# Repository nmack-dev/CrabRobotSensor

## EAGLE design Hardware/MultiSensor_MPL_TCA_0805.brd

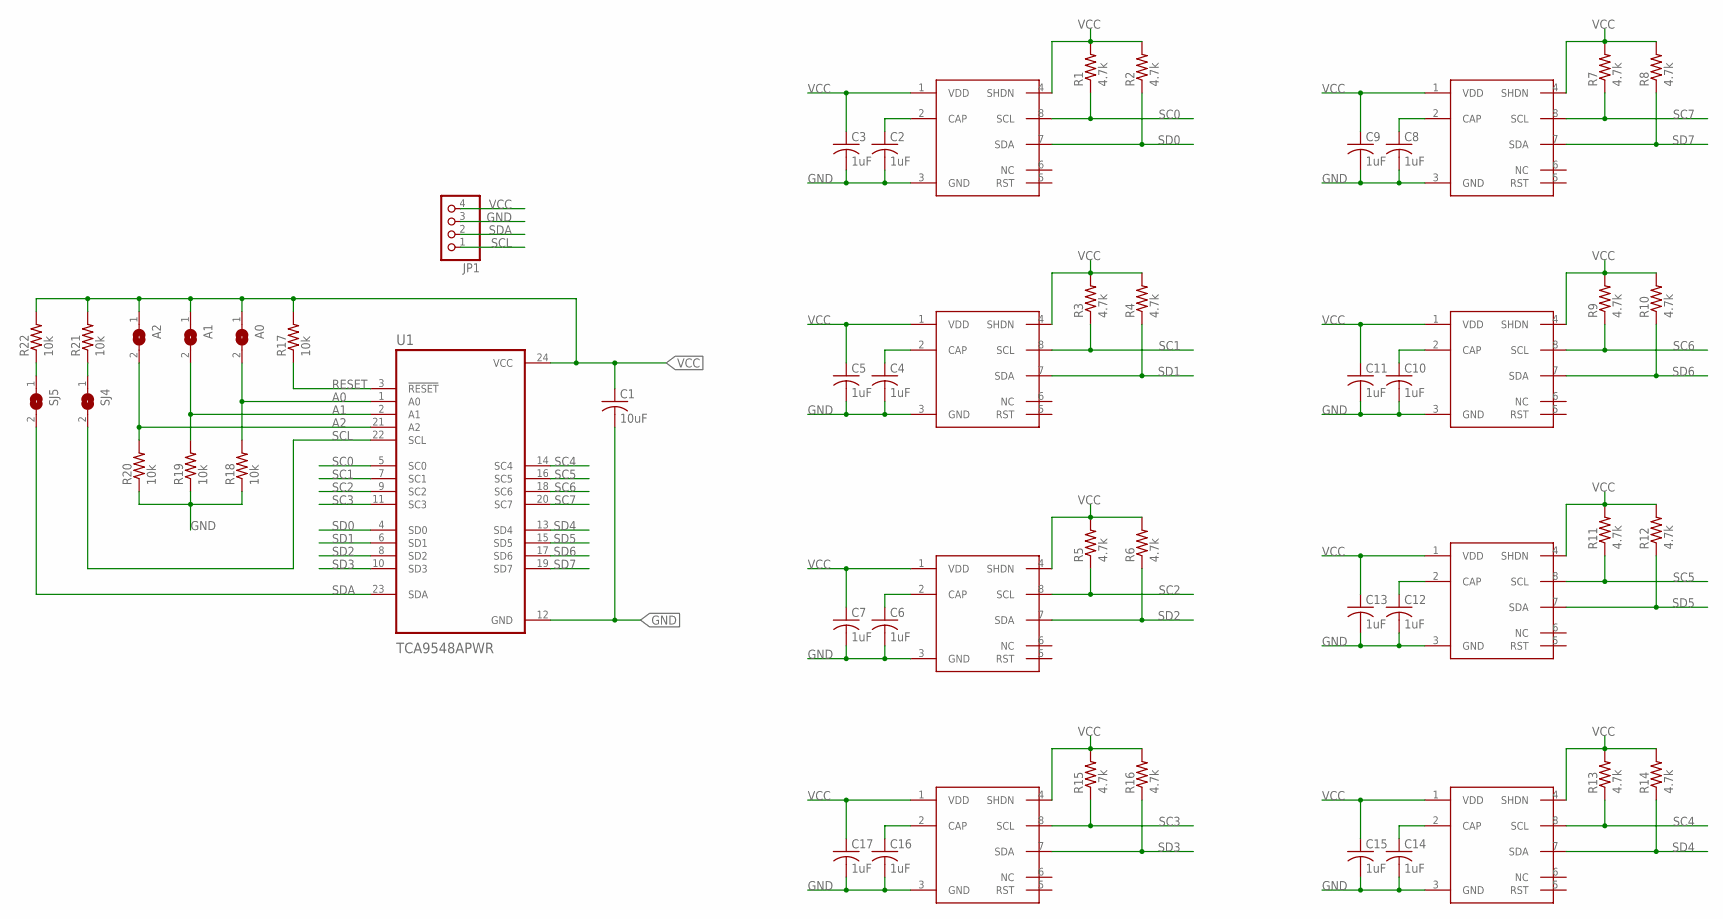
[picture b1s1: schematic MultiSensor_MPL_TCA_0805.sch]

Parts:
A0, A1, A2: SJ
B1, B2, B3, B4, B5, B6, B7, B8: MPL115A2T1
C1: 10uF; C1206
C2, C3, C4, C5, C6, C7, C8, C9, C10, C11, C12, C13, C14, C15, C16, C17: 1uF; C0805
JP1: PINHD-1X4; 1X04
R1, R2, R3, R4, R5, R6, R7, R8, R9, R10, R11, R12, R13, R14, R15, R16: 4.7k; R0805
R17, R18, R19, R20, R21, R22: 10k; R0805
SJ4, SJ5: SJ
U1: TCA9548APWR; SOP65P640X120-24N

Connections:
A0: A0.2, R18.2, U1.1 (A0)
A1: A1.2, R19.2, U1.2 (A1)
A2: A2.2, R20.2, U1.21 (A2)
CAP1: B1.2 (CAP), C2.1
CAP2: B2.2 (CAP), C4.1
CAP3: B3.2 (CAP), C6.1
CAP4: B8.2 (CAP), C16.1
CAP5: B7.2 (CAP), C14.1
CAP6: B6.2 (CAP), C12.1
CAP7: B5.2 (CAP), C10.1
CAP8: B4.2 (CAP), C8.1
GND: B1.3 (GND), B2.3 (GND), B3.3 (GND), B4.3 (GND), B5.3 (GND), B6.3 (GND), B7.3 (GND), B8.3 (GND), C1.2, C2.2, C3.2, C4.2, C5.2, C6.2, C7.2, C8.2, C9.2, C10.2, C11.2, C12.2, C13.2, C14.2, C15.2, C16.2, C17.2, JP1.3, R18.1, R19.1, R20.1, U1.12 (GND)
unnamed: R22.1, SJ5.1
unnamed: R21.1, SJ4.1
RESET: R17.1, U1.3 (!RESET)
SC0: B1.8 (SCL), R1.1, U1.5 (SC0)
SC1: B2.8 (SCL), R3.1, U1.7 (SC1)
SC2: B3.8 (SCL), R5.1, U1.9 (SC2)
SC3: B8.8 (SCL), R15.1, U1.11 (SC3)
SC4: B7.8 (SCL), R13.1, U1.14 (SC4)
SC5: B6.8 (SCL), R11.1, U1.16 (SC5)
SC6: B5.8 (SCL), R9.1, U1.18 (SC6)
SC7: B4.8 (SCL), R7.1, U1.20 (SC7)
SCL: JP1.1, SJ4.2, U1.22 (SCL)
SD0: B1.7 (SDA), R2.1, U1.4 (SD0)
SD1: B2.7 (SDA), R4.1, U1.6 (SD1)
SD2: B3.7 (SDA), R6.1, U1.8 (SD2)
SD3: B8.7 (SDA), R16.1, U1.10 (SD3)
SD4: B7.7 (SDA), R14.1, U1.13 (SD4)
SD5: B6.7 (SDA), R12.1, U1.15 (SD5)
SD6: B5.7 (SDA), R10.1, U1.17 (SD6)
SD7: B4.7 (SDA), R8.1, U1.19 (SD7)
SDA: JP1.2, SJ5.2, U1.23 (SDA)
VCC: A0.1, A1.1, A2.1, B1.1 (VDD), B1.4 (SHDN), B2.1 (VDD), B2.4 (SHDN), B3.1 (VDD), B3.4 (SHDN), B4.1 (VDD), B4.4 (SHDN), B5.1 (VDD), B5.4 (SHDN), B6.1 (VDD), B6.4 (SHDN), B7.1 (VDD), B7.4 (SHDN), B8.1 (VDD), B8.4 (SHDN), C1.1, C3.1, C5.1, C7.1, C9.1, C11.1, C13.1, C15.1, C17.1, JP1.4, R1.2, R2.2, R3.2, R4.2, R5.2, R6.2, R7.2, R8.2, R9.2, R10.2, R11.2, R12.2, R13.2, R14.2, R15.2, R16.2, R17.2, R21.2, R22.2, U1.24 (VCC)

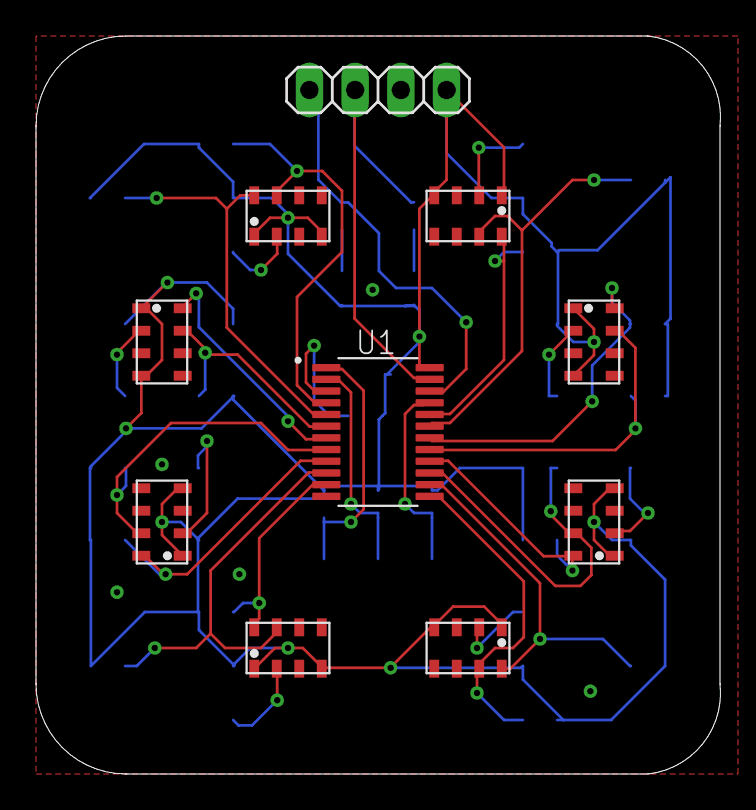
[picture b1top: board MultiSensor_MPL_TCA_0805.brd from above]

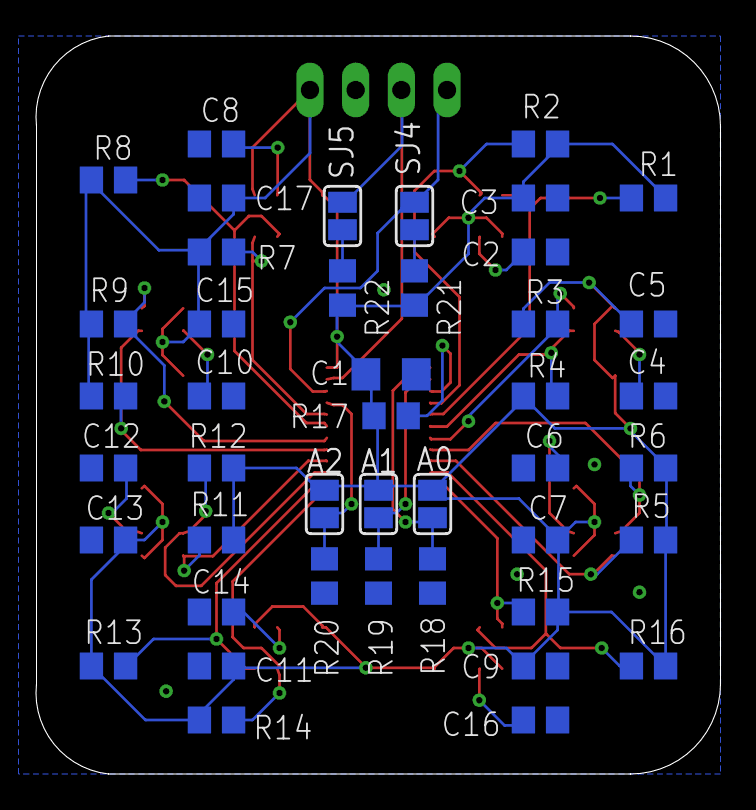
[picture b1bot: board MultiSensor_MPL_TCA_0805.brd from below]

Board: 2 copper layers, 38.0 x 41.0 mm, 54 parts (44 on the bottom side), 34 nets.

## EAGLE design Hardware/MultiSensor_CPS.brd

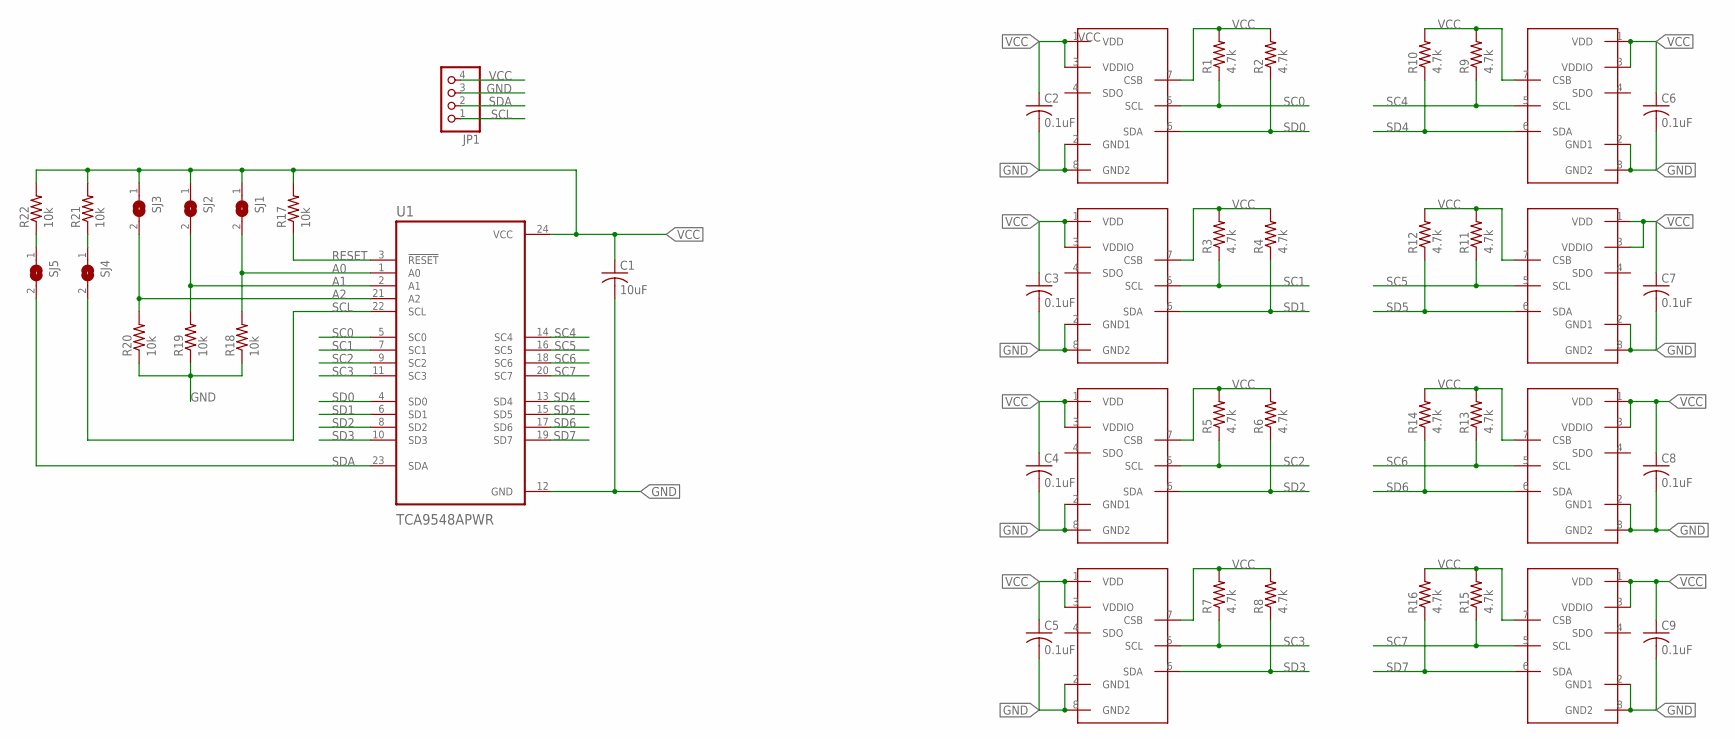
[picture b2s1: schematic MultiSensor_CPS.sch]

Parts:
B1, B2, B3, B4, B5, B6, B8, B9: CPS123
C1: 10uF; C0805
C2, C3, C4, C5, C6, C7, C8, C9: 0.1uF; C0805
JP1: PINHD-1X4; 1X04
R1, R2, R3, R4, R5, R6, R7, R8, R9, R10, R11, R12, R13, R14, R15, R16: 4.7k; R0805
R17, R18, R19, R20, R21, R22: 10k; R0805
SJ1, SJ2, SJ3, SJ4, SJ5: SJ
U1: TCA9548APWR; SOP65P640X120-24N

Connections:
A0: R18.2, SJ1.2, U1.1 (A0)
A1: R19.2, SJ2.2, U1.2 (A1)
A2: R20.2, SJ3.2, U1.21 (A2)
GND: B1.2 (GND1), B1.8 (GND2), B2.2 (GND1), B2.8 (GND2), B3.2 (GND1), B3.8 (GND2), B4.2 (GND1), B4.8 (GND2), B5.2 (GND1), B5.8 (GND2), B6.2 (GND1), B6.8 (GND2), B8.2 (GND1), B8.8 (GND2), B9.2 (GND1), B9.8 (GND2), C1.2, C2.2, C3.2, C4.2, C5.2, C6.2, C7.2, C8.2, C9.2, JP1.3, R18.1, R19.1, R20.1, U1.12 (GND)
unnamed: R22.1, SJ5.1
unnamed: R21.1, SJ4.1
RESET: R17.1, U1.3 (!RESET)
SC0: B5.5 (SCL), R1.1, U1.5 (SC0)
SC1: B1.5 (SCL), R3.1, U1.7 (SC1)
SC2: B2.5 (SCL), R5.1, U1.9 (SC2)
SC3: B9.5 (SCL), R7.1, U1.11 (SC3)
SC4: B6.5 (SCL), R9.1, U1.14 (SC4)
SC5: B4.5 (SCL), R11.1, U1.16 (SC5)
SC6: B3.5 (SCL), R13.1, U1.18 (SC6)
SC7: B8.5 (SCL), R15.1, U1.20 (SC7)
SCL: JP1.1, SJ4.2, U1.22 (SCL)
SD0: B5.6 (SDA), R2.1, U1.4 (SD0)
SD1: B1.6 (SDA), R4.1, U1.6 (SD1)
SD2: B2.6 (SDA), R6.1, U1.8 (SD2)
SD3: B9.6 (SDA), R8.1, U1.10 (SD3)
SD4: B6.6 (SDA), R10.1, U1.13 (SD4)
SD5: B4.6 (SDA), R12.1, U1.15 (SD5)
SD6: B3.6 (SDA), R14.1, U1.17 (SD6)
SD7: B8.6 (SDA), R16.1, U1.19 (SD7)
SDA: JP1.2, SJ5.2, U1.23 (SDA)
VCC: B1.1 (VDD), B1.3 (VDDIO), B1.7 (CSB), B2.1 (VDD), B2.3 (VDDIO), B2.7 (CSB), B3.1 (VDD), B3.3 (VDDIO), B3.7 (CSB), B4.1 (VDD), B4.3 (VDDIO), B4.7 (CSB), B5.1 (VDD), B5.3 (VDDIO), B5.7 (CSB), B6.1 (VDD), B6.3 (VDDIO), B6.7 (CSB), B8.1 (VDD), B8.3 (VDDIO), B8.7 (CSB), B9.1 (VDD), B9.3 (VDDIO), B9.7 (CSB), C1.1, C2.1, C3.1, C4.1, C5.1, C6.1, C7.1, C8.1, C9.1, JP1.4, R1.2, R2.2, R3.2, R4.2, R5.2, R6.2, R7.2, R8.2, R9.2, R10.2, R11.2, R12.2, R13.2, R14.2, R15.2, R16.2, R17.2, R21.2, R22.2, SJ1.1, SJ2.1, SJ3.1, U1.24 (VCC)

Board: 2 copper layers, 46 parts (36 on the bottom side), 26 nets, no tracks yet.

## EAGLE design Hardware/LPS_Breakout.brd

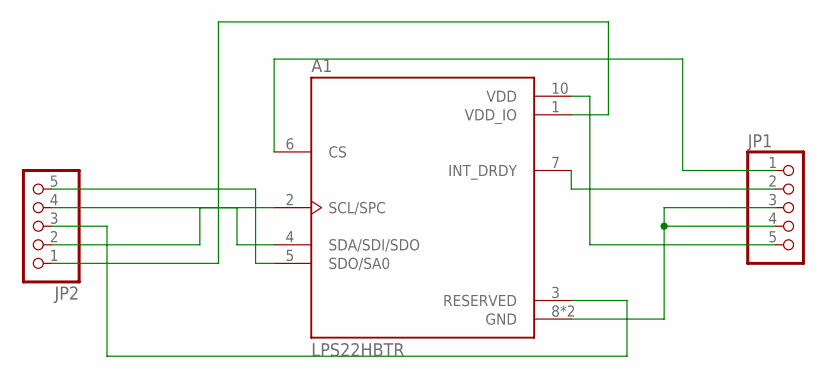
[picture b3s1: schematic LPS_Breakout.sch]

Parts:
A1: LPS22HBTR; PQFN50P200X200X80-10N
JP1, JP2: PINHD-1X5; 1X05

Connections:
unnamed: A1.1 (VDD_IO), JP2.1
unnamed: A1.2 (SCL/SPC), JP2.2
unnamed: A1.3 (RESERVED), JP2.3
unnamed: A1.4 (SDA/SDI/SDO), JP2.4
unnamed: A1.5 (SDO/SA0), JP2.5
unnamed: A1.6 (CS), JP1.1
unnamed: A1.7 (INT_DRDY), JP1.2
unnamed: A1.8 (GND), A1.9 (GND), JP1.3, JP1.4
unnamed: A1.10 (VDD), JP1.5

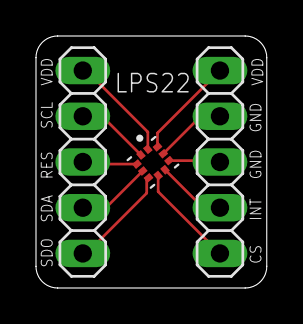
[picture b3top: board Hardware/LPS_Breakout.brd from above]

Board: 2 copper layers, 12.8 x 14.0 mm, 3 parts (0 on the bottom side), 9 nets.

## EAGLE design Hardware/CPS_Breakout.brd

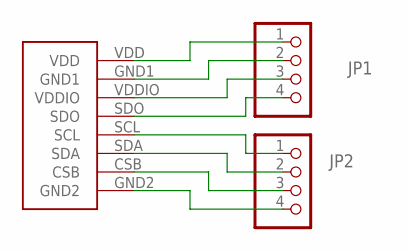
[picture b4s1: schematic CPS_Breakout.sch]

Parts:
B1: CPS123
JP1, JP2: PINHD-1X4; 1X04

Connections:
unnamed: B1.GND1, JP1.2
unnamed: B1.VDD, JP1.1
unnamed: B1.VDDIO, JP1.3
unnamed: B1.SDO, JP1.4
unnamed: B1.SCL, JP2.1
unnamed: B1.SDA, JP2.2
unnamed: B1.CSB, JP2.3
unnamed: B1.GND2, JP2.4

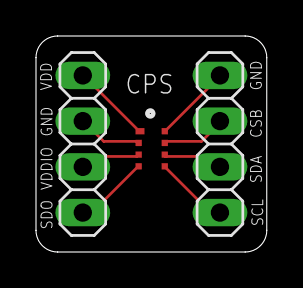
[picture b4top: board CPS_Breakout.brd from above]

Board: 2 copper layers, 12.8 x 12.0 mm, 3 parts (0 on the bottom side), 8 nets.

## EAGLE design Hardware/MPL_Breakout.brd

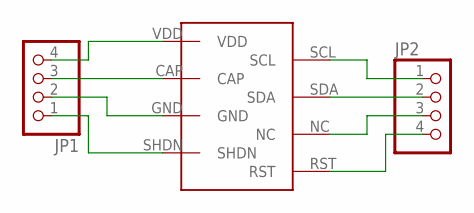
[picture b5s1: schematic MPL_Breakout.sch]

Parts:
B1: MPL115A2T1
JP1, JP2: PINHD-1X4; 1X04

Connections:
unnamed: B1.VDD, JP1.4
unnamed: B1.CAP, JP1.3
unnamed: B1.GND, JP1.2
unnamed: B1.SHDN, JP1.1
unnamed: B1.RST, JP2.4
unnamed: B1.NC, JP2.3
unnamed: B1.SDA, JP2.2
unnamed: B1.SCL, JP2.1

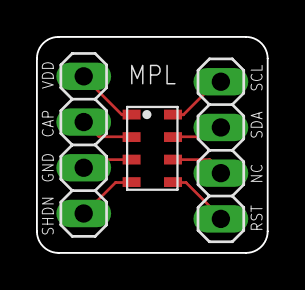
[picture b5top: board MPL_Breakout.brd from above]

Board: 2 copper layers, 12.8 x 12.0 mm, 3 parts (0 on the bottom side), 8 nets.

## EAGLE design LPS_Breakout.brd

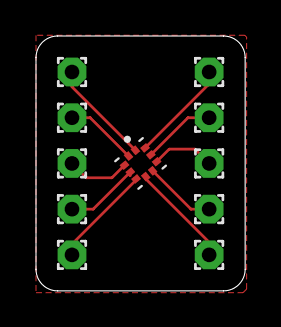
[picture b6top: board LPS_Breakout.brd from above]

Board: 2 copper layers, 11.6 x 14.2 mm, 11 parts (0 on the bottom side), 9 nets.

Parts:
A1: LPS22HBTR; PQFN50P200X200X80-10N
PAD1, PAD2, PAD3, PAD4, PAD5, PAD6, PAD7, PAD8, PAD9, PAD10: 1,6/0,8

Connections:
unnamed: A1.1, PAD1.1
unnamed: A1.2, PAD2.1
unnamed: A1.3, PAD3.1
unnamed: A1.4, PAD4.1
unnamed: A1.5, PAD5.1
unnamed: A1.6, PAD6.1
unnamed: A1.7, PAD7.1
unnamed: A1.8, A1.9, PAD8.1, PAD9.1
unnamed: A1.10, PAD10.1

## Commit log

2021-02-11 added .INO files from Gabe
2021-02-17 added Adafruit example code for mux
    base line test that the mux is working
2021-03-01 Added firmware folder & main program for LPS22 barometer
2021-03-02 added breakout boards for barometers
2021-03-02 new hardware file
2021-03-02 Rename CPS_Breakout.brd to Hardware/CPS_Breakout.brd
2021-03-02 Rename CPS_Breakout.sch to Hardware/CPS_Breakout.sch
2021-03-02 Rename LPS_Breakout.brd to Hardware/LPS_Breakout.brd
2021-03-02 Rename LPS_Breakout.sch to Hardware/LPS_Breakout.sch
2021-03-02 Rename MPL_Breakout.brd to Hardware/MPL_Breakout.brd
2021-03-02 Rename MPL_Breakout.sch to Hardware/MPL_Breakout.sch
2021-03-03 Add wire.begin()
2021-03-03 Design for base, mounting plate, and support
2021-03-03 Added test file
2021-03-03 Removed test
2021-03-04 Deleted old code. Added code that populates barometer readings in real time.
2021-03-05 add print function to check reading
2021-03-05 add testfile
2021-03-05 remove testfile
2021-03-05 Updated design for mounting plate
2021-03-08 Bug fixes, started work on force-torque calculations, moved files
2021-03-15 Bug fixes on calibration constant script. Continued firmware development.
2021-03-16 Finished untested firmware for LPS22-based sensor
2021-03-22 updated pinheaders and names
2021-03-22 draft schematic with CPS
2021-03-25 components placed in draft layout
2021-03-26 prelim routing
2021-03-27 init library for CPS123
2021-03-27 based on CPS120 library
    please review, not 100% confident on shifting math to convert reading
    I think it's also possible to just get pressure reading since we don't need temperature
2021-03-29 Created file structure for the firmware
2021-03-31 added bypass caps, routing undone
2021-03-31 prelim schematic, based on datasheet
2021-04-03 layout and routing of board
2021-04-05 using TCA and 0805 components
2021-04-05 using PCA and 0805 components
2021-04-06 Redesigned Base and Mounting Plates
2021-04-06 bulk bypass cap changed to from 0805 to 1206
2021-04-06 Updated design for support
2021-04-12 Initial firmware for MPL115A2 config
